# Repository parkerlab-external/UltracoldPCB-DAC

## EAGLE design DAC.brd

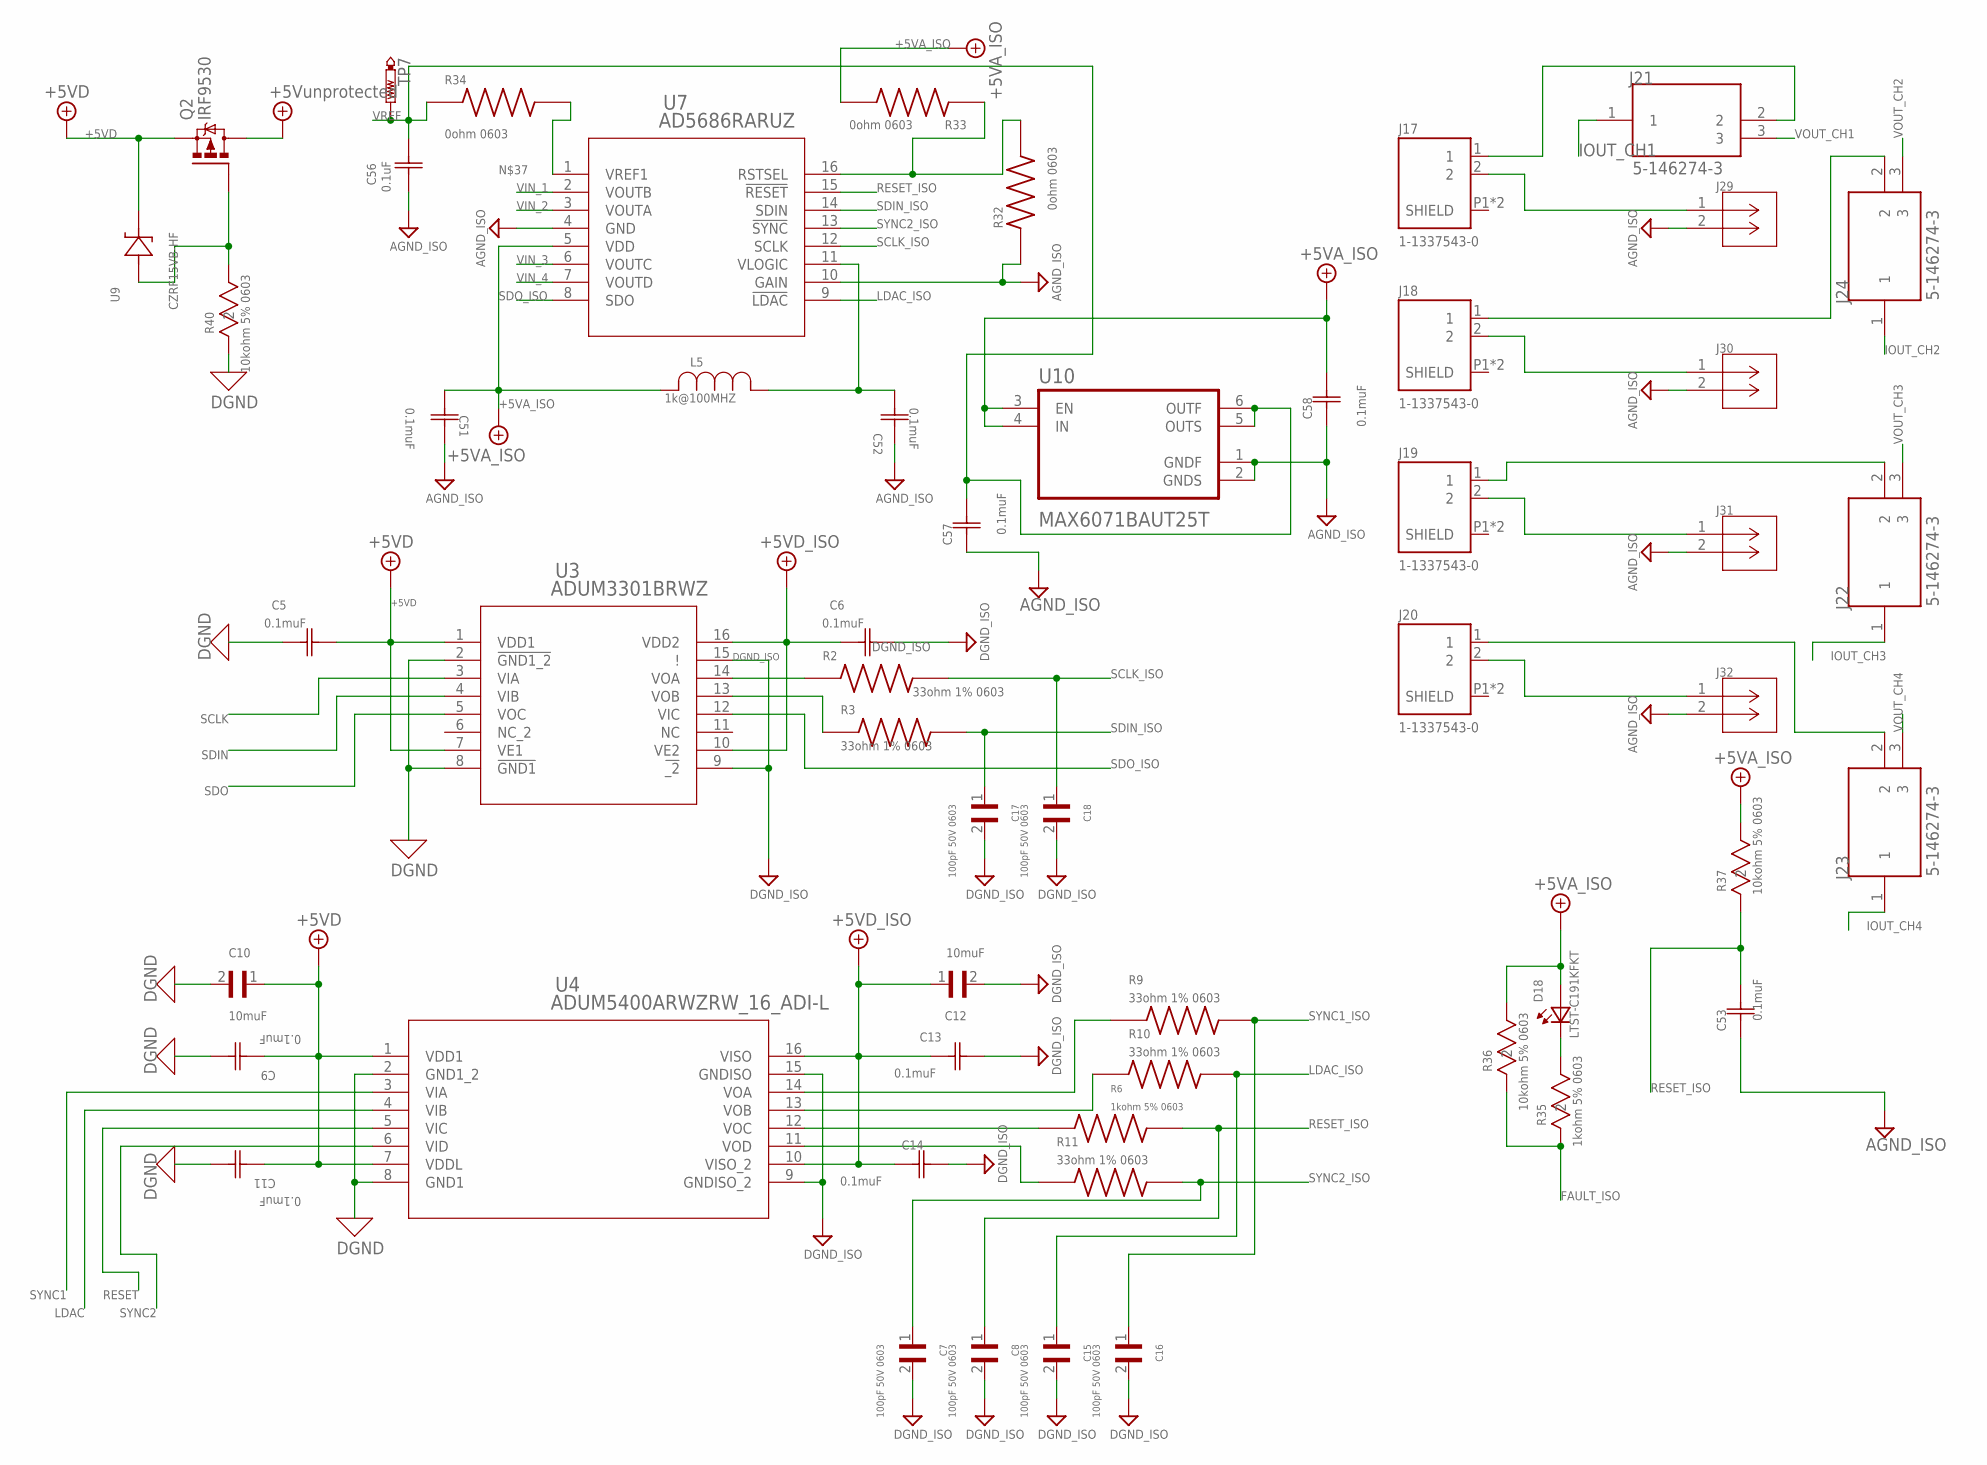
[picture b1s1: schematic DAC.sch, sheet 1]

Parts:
C5, C6, C9, C11, C13, C14, C51, C52, C53, C56, C57, C58: 0.1muF; G-188_MUR
C7, C8, C15, C16, C17, C18: 100pF 50V 0603; CAPC1608X90N
C10, C12: 10muF; CAPC2012X135N
D18: LTST-C191KFKT; 0603
J17, J18, J19, J20: 1-1337543-0; CONN_1-1337543-0
J21, J22, J23, J24: 5-146274-3; TE_5-146274-3
J29, J30, J31, J32: 61300211121; CONN_61300211121_WRE
L5: 1k@100MHZ; IND_BLM18_0603_MUR
Q2: IRF9530; TO220BV
R2, R3, R9, R10, R11: 33ohm 1% 0603; RESC1508X50N
R6: 1kohm 5% 0603; RESC1608X55N
R32, R33, R34: 0ohm 0603; RESC1608X55N
R35: 1kohm 5% 0603; RC0603N_PAN
R36, R37, R40: 10kohm 5% 0603; RC0603N_PAN
TP7: PTR1B1,27; B1,27
U3: ADUM3301BRWZ; RW_16_ADI
U4: ADUM5400ARWZRW_16_ADI-L; RW_16_ADI-L
U7: AD5686RARUZ; RU-16_ADI
U9: CZRF15VB-HF; CZRF
U10: MAX6071BAUT25T; SOT95P280X145-6N

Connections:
+5VA_ISO: C51.1, C58.2, D18.2 (A2), L5.2, R33.2, R36.1, R37.1, U7.5 (VDD), U10.3 (EN), U10.4 (IN); also elsewhere on the board
+5VD: C5.2, C9.1, C10.1, C11.1, Q2.S, U3.1 (VDD1), U3.7 (VE1), U4.1 (VDD1), U4.7 (VDDL), U9.1; also elsewhere on the board
+5VD_ISO: C6.1, C12.1, C13.1, C14.1, U3.10 (VE2), U3.16 (VDD2), U4.10 (VISO_2), U4.16 (VISO); also elsewhere on the board
+5V_UN: Q2.D
AGND_ISO: C51.2, C52.2, C53.1, C56.1, C57.1, C58.1, J29.2, J30.2, J31.2, J32.2, R32.1, U7.4 (GND), U7.10 (GAIN), U10.1 (GNDF), U10.2 (GNDS); also elsewhere on the board
DGND: C5.1, C9.2, C10.2, C11.2, R40.2, U3.2 (!GND1_2), U3.8 (!GND1), U4.2 (GND1_2), U4.8 (GND1); also elsewhere on the board
DGND_ISO: C6.2, C7.2, C8.2, C12.2, C13.2, C14.2, C15.2, C16.2, C17.2, C18.2, U3.9 (!_2), U3.15 (!), U4.9 (GNDISO_2), U4.15 (GNDISO); also elsewhere on the board
FAULT_ISO: R35.2, R36.2; also elsewhere on the board
IOUT_CH1: J21.1; also elsewhere on the board
IOUT_CH2: J24.1; also elsewhere on the board
IOUT_CH3: J22.1; also elsewhere on the board
IOUT_CH4: J23.1; also elsewhere on the board
LDAC: U4.4 (VIB); also elsewhere on the board
LDAC_ISO: C15.1, R10.2, U7.9 (!LDAC)
unnamed: C52.1, L5.1, U7.11 (VLOGIC)
unnamed: R9.1, U4.14 (VOA)
unnamed: R2.1, U3.14 (VOA)
unnamed: R3.1, U3.13 (VOB)
unnamed: R10.1, U4.13 (VOB)
unnamed: R6.1, U4.12 (VOC)
unnamed: R11.1, U4.11 (VOD)
unnamed: J17.2, J29.1
unnamed: D18.1 (K2), R35.1
unnamed: J18.2, J30.1
unnamed: R34.2, U7.1 (VREF1)
unnamed: J17.1, J21.2
unnamed: J18.1, J24.2
unnamed: J19.2, J31.1
unnamed: J19.1, J22.2
unnamed: J20.1, J23.2
unnamed: J20.2, J32.1
unnamed: Q2.G, R40.1, U9.2
unnamed: R32.2, R33.1, U7.16 (RSTSEL)
RESET: U4.5 (VIC); also elsewhere on the board
RESET_ISO: C8.1, C53.2, R6.2, R37.2, U7.15 (!RESET); also elsewhere on the board
SCLK: U3.3 (VIA); also elsewhere on the board
SCLK_ISO: C18.1, R2.2, U7.12 (SCLK); also elsewhere on the board
SDIN: U3.4 (VIB); also elsewhere on the board
SDIN_ISO: C17.1, R3.2, U7.14 (SDIN); also elsewhere on the board
SDO: U3.5 (VOC); also elsewhere on the board
SDO_ISO: U3.12 (VIC), U7.8 (SDO); also elsewhere on the board
SYNC1: U4.3 (VIA); also elsewhere on the board
SYNC1_ISO: C16.1, R9.2; also elsewhere on the board
SYNC2: U4.6 (VID); also elsewhere on the board
SYNC2_ISO: C7.1, R11.2, U7.13 (!SYNC)
VIN_1: U7.2 (VOUTB); also elsewhere on the board
VIN_2: U7.3 (VOUTA); also elsewhere on the board
VIN_3: U7.6 (VOUTC); also elsewhere on the board
VIN_4: U7.7 (VOUTD); also elsewhere on the board
VOUT_CH1: J21.3; also elsewhere on the board
VOUT_CH2: J24.3; also elsewhere on the board
VOUT_CH3: J22.3; also elsewhere on the board
VOUT_CH4: J23.3; also elsewhere on the board
VREF: C56.2, C57.2, R34.1, TP7.TP, U10.5 (OUTS), U10.6 (OUTF); also elsewhere on the board

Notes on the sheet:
0.1uF

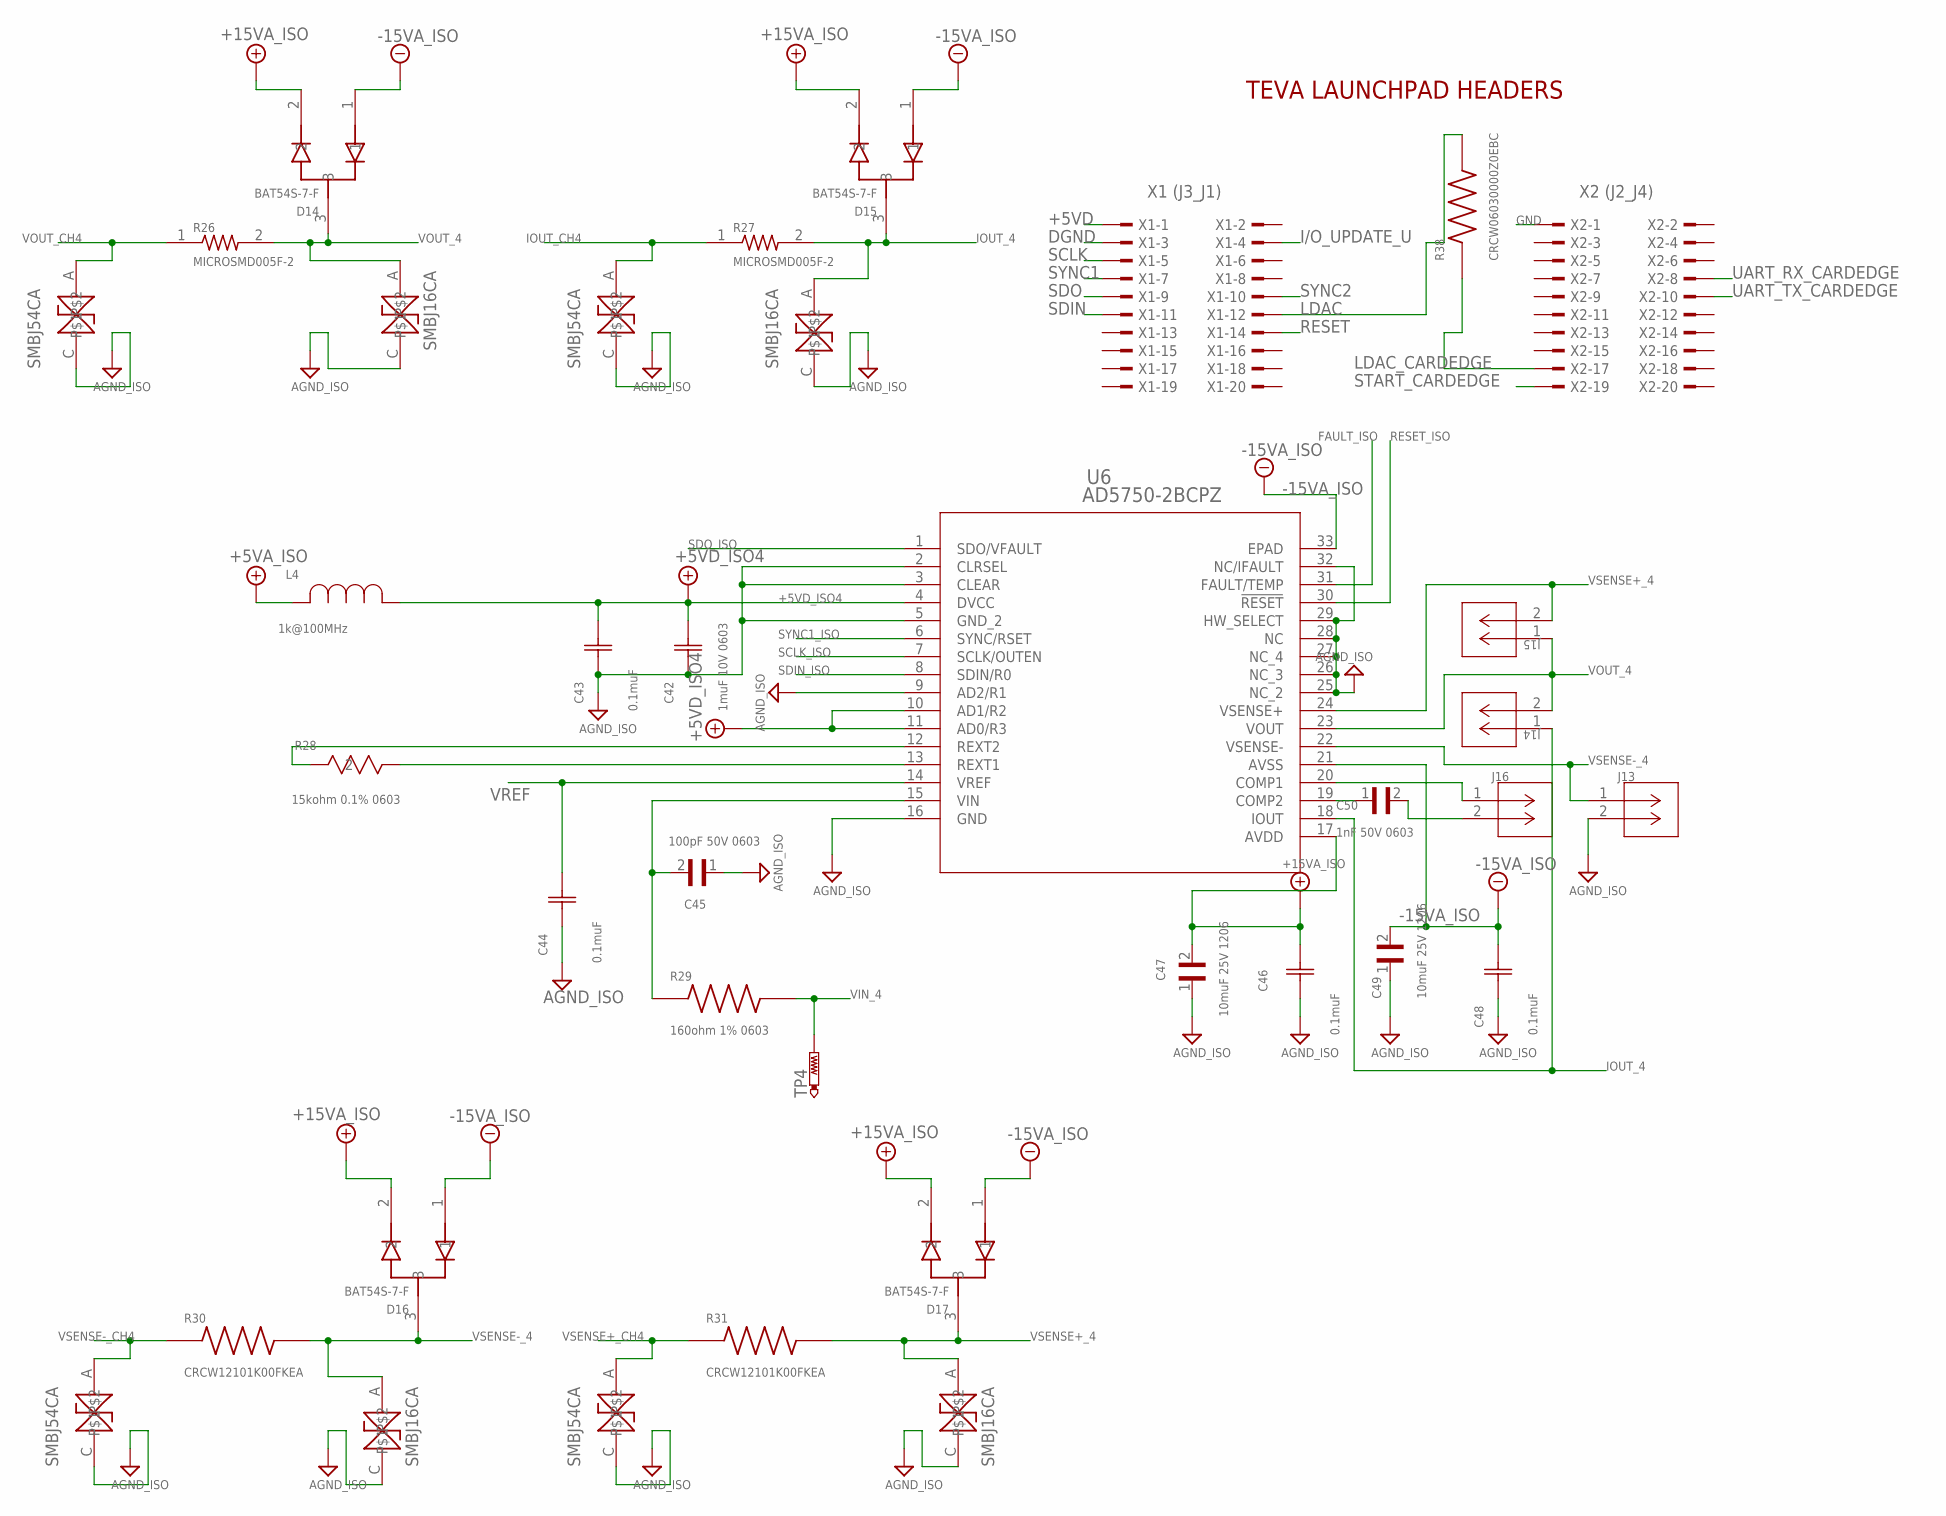
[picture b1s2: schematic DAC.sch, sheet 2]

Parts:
C42: 1muF 10V 0603; CAPC17595_90N_KEM
C43, C44, C46, C48: 0.1muF; G-188_MUR
C45: 100pF 50V 0603; CAPC1608X90N
C47, C49: 10muF 25V 1206; CAPC3216X180N
C50: 1nF 50V 0603; CAPC1608X90N
D14, D15, D16, D17: BAT54S-7-F; SOT95P240X110-3N
J13, J14, J15, J16: 61300211121; CONN_61300211121_WRE
L4: 1k@100MHz; IND_BLM18_0603_MUR
R26, R27: MICROSMD005F-2; RESC3125X65N
R28: 15kohm 0.1% 0603; RC0603N_PAN
R29: 160ohm 1% 0603; RESC1608X55N
R30, R31: CRCW12101K00FKEA; RESC3225X60N
R38: CRCW06030000Z0EBC; RESC1608X55N
TP4: PTR1B1,27; B1,27
TV1, TV2, TV4: 54_SMBJ54CA; DIOM5436X220N
TV3: SMBJ54CA; DIOM5436X220N
TV17, TV18, TV19, TV20: SMBJ16CA; DIOM5436X220N
U6: AD5750-2BCPZ; CP_32_7_ADI
X1: X1 (J3_J1); TSW-110-XX-G-D
X2: X2 (J2_J4); TSW-110-XX-G-D

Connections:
+5VA_ISO: L4.2; also elsewhere on the board
+5VD: X1.1; also elsewhere on the board
+5VD_ISO4: C42.2, C43.2, L4.1, U6.4 (DVCC), U6.10 (AD1/R2), U6.11 (AD0/R3)
+15VA_ISO: C46.2, C47.2, D14.2, D15.2, D16.2, D17.2, U6.17 (AVDD); also elsewhere on the board
-15VA_ISO: C48.2, C49.2, D14.1, D15.1, D16.1, D17.1, U6.21 (AVSS), U6.33 (EPAD); also elsewhere on the board
AGND_ISO: C42.1, C43.1, C44.1, C45.1, C46.1, C47.1, C48.1, C49.1, J13.2, TV1.C, TV2.C, TV3.C, TV4.C, TV17.C, TV18.C, TV19.C, TV20.C, U6.2 (CLRSEL), U6.3 (CLEAR), U6.5 (GND_2), U6.9 (AD2/R1), U6.16 (GND), U6.25 (NC_2), U6.26 (NC_3), U6.27 (NC_4), U6.28 (NC), U6.29 (HW_SELECT), U6.32 (NC/IFAULT); also elsewhere on the board
DGND: X1.3; also elsewhere on the board
FAULT_ISO: U6.31 (FAULT/TEMP); also elsewhere on the board
GND: X2.1
I/O_UPDATE_U: X1.4
IOUT_4: D15.3, J14.1, R27.2, TV18.A, U6.18 (IOUT)
IOUT_CH4: R27.1, TV2.A; also elsewhere on the board
LDAC: R38.2, X1.12; also elsewhere on the board
LDAC_CARDEDGE: R38.1, X2.17
unnamed: R28.2, U6.12 (REXT2)
unnamed: R28.1, U6.13 (REXT1)
unnamed: C45.2, R29.1, U6.15 (VIN)
unnamed: C50.1, U6.19 (COMP2)
unnamed: J16.1, U6.20 (COMP1)
unnamed: C50.2, J16.2
RESET: X1.14; also elsewhere on the board
RESET_ISO: U6.30 (!RESET); also elsewhere on the board
SCLK: X1.5; also elsewhere on the board
SCLK_ISO: U6.7 (SCLK/OUTEN); also elsewhere on the board
SDIN: X1.11; also elsewhere on the board
SDIN_ISO: U6.8 (SDIN/R0); also elsewhere on the board
SDO: X1.9; also elsewhere on the board
SDO_ISO: U6.1 (SDO/VFAULT); also elsewhere on the board
START_CARDEDGE: X2.19
SYNC1: X1.7; also elsewhere on the board
SYNC1_ISO: U6.6 (SYNC/RSET); also elsewhere on the board
SYNC2: X1.10; also elsewhere on the board
UART_RX_CARDEDGE: X2.8
UART_TX_CARDEDGE: X2.10
VIN_4: R29.2, TP4.TP; also elsewhere on the board
VOUT_4: D14.3, J14.2, J15.1, R26.2, TV17.A, U6.23 (VOUT)
VOUT_CH4: R26.1, TV1.A; also elsewhere on the board
VREF: C44.2, U6.14 (VREF); also elsewhere on the board
VSENSE+_4: D17.3, J15.2, R31.2, TV20.A, U6.24 (VSENSE+)
VSENSE+_CH4: R31.1, TV4.A
VSENSE-_4: D16.3, J13.1, R30.2, TV19.A, U6.22 (VSENSE-)
VSENSE-_CH4: R30.1, TV3.A

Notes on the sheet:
TEVA LAUNCHPAD HEADERS
SMBJ16CA
SMBJ54CA

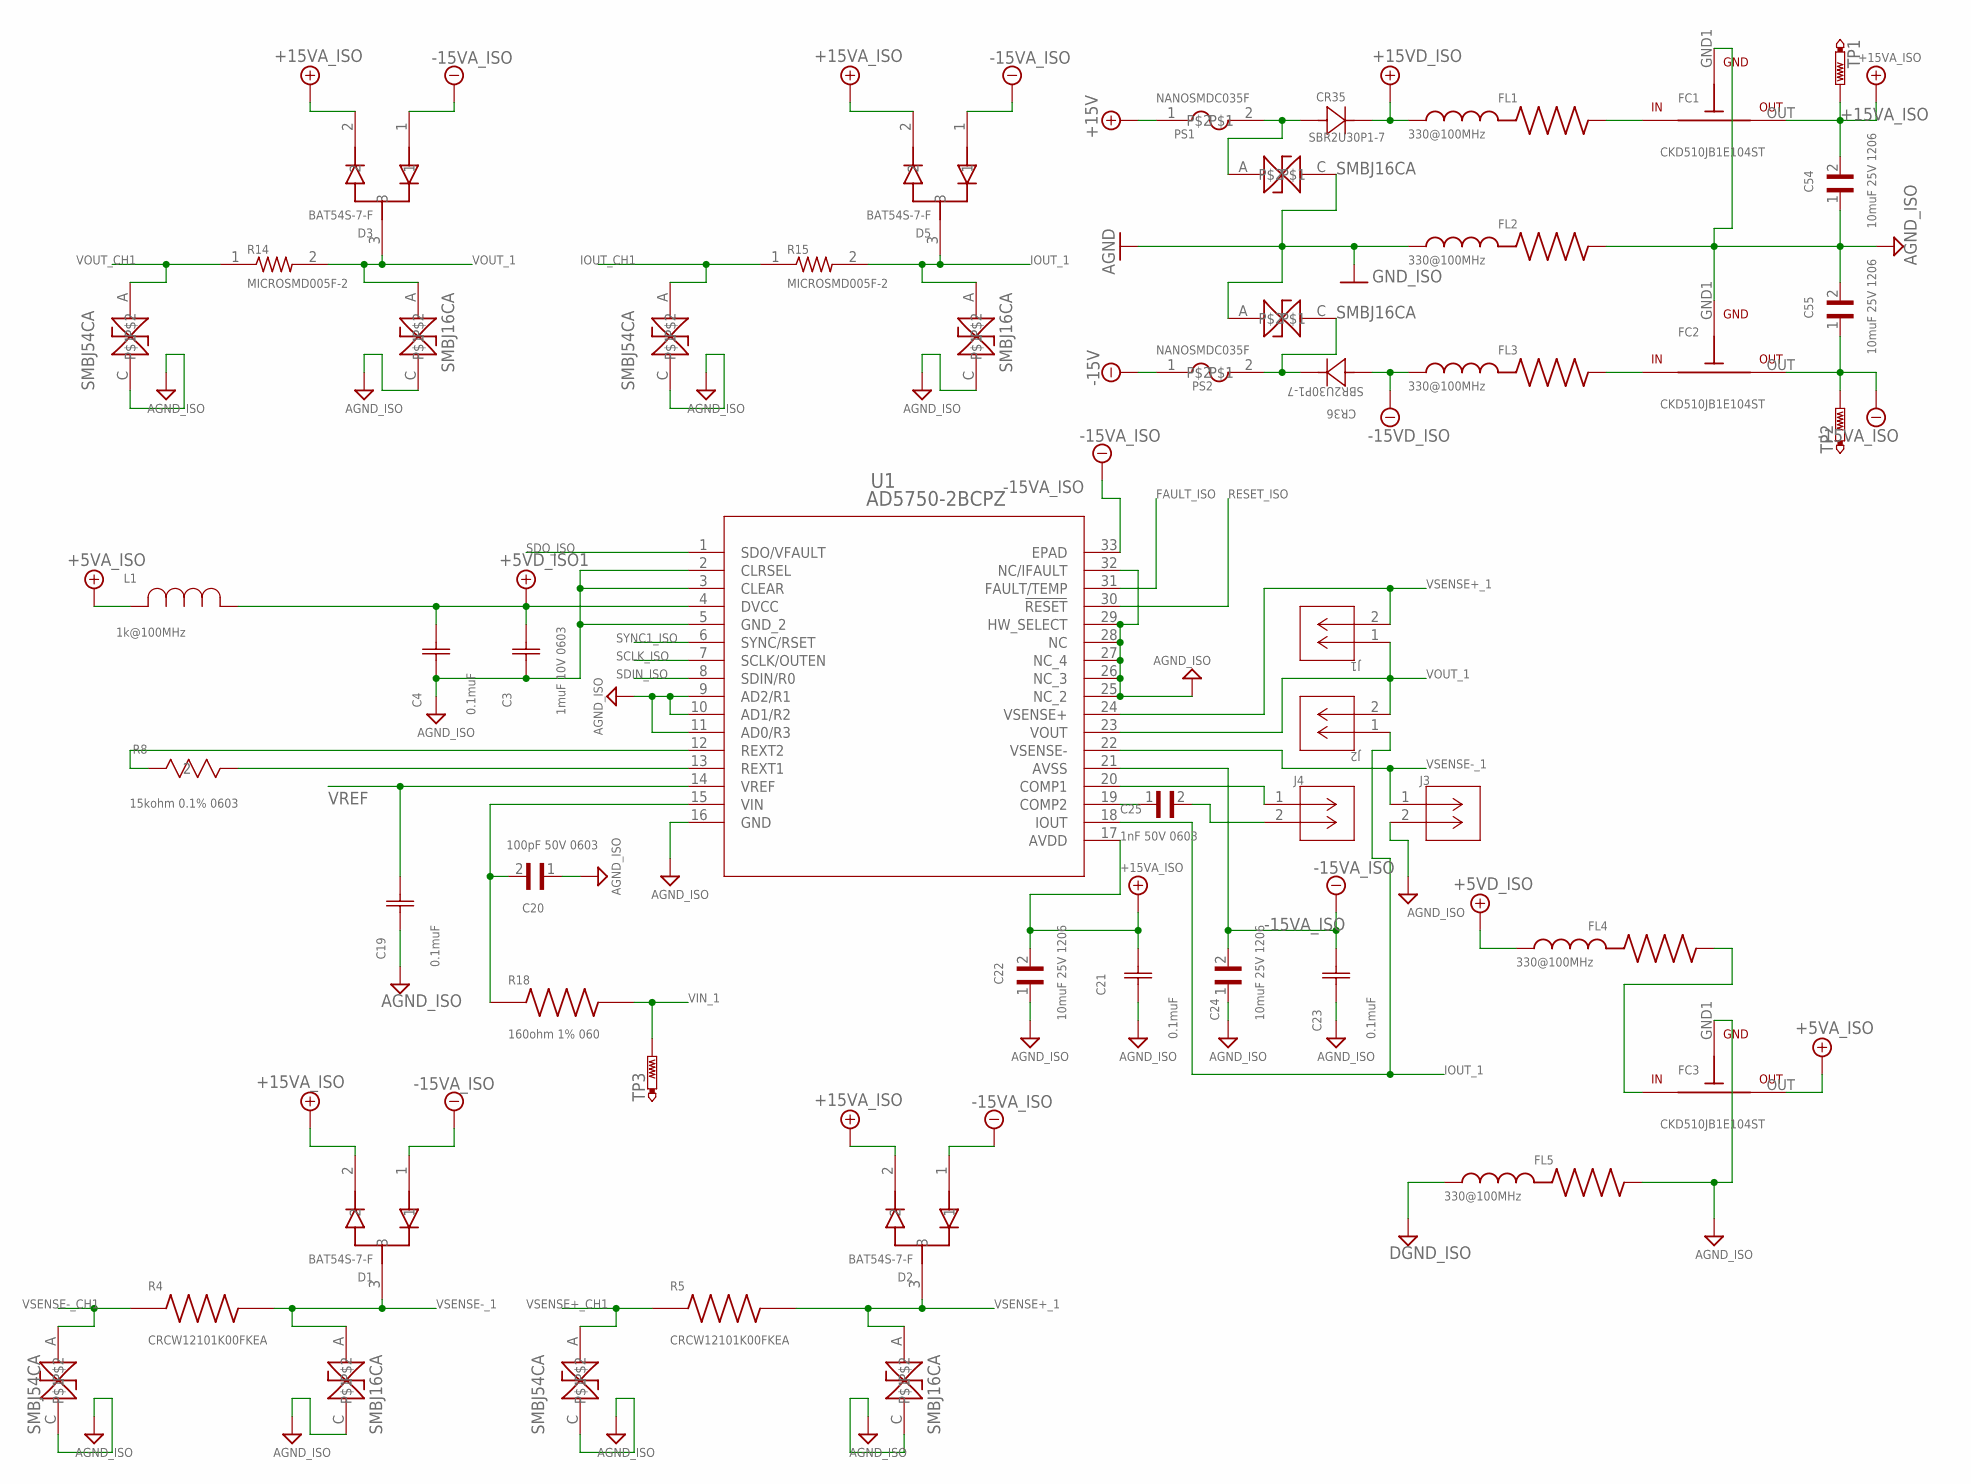
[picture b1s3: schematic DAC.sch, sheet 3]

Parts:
C3: 1muF 10V 0603; CAPC17595_90N_KEM
C4, C19, C21, C23: 0.1muF; G-188_MUR
C20: 100pF 50V 0603; CAPC1608X90N
C22, C24, C54, C55: 10muF 25V 1206; CAPC3216X180N
C25: 1nF 50V 0603; CAPC1608X90N
CR35, CR36: SBR2U30P1-7; DIODE_SBR3M30P1_1P78X2P8_DIO
D1, D2, D3, D5: BAT54S-7-F; SOT95P240X110-3N
FC1, FC2, FC3: F1-4; FCAP
FL1, FL2, FL3, FL4, FL5: 330@100MHz; BEADC2012X105N
J1, J2, J3, J4: 61300211121; CONN_61300211121_WRE
L1: 1k@100MHz; IND_BLM18_0603_MUR
PS1, PS2: POLYSWITCH; RESC3115X65N
R4, R5: CRCW12101K00FKEA; RESC3225X60N
R8: 15kohm 0.1% 0603; RC0603N_PAN
R14, R15: MICROSMD005F-2; RESC3125X65N
R18: 160ohm 1% 060; RESC1608X55N
TP1, TP2, TP3: PTR1B1,27; B1,27
TV5, TV6, TV7, TV8: 54_SMBJ54CA; DIOM5436X220N
TV21, TV22, TV23, TV24, TV33, TV34: SMBJ16CA; DIOM5436X220N
U1: AD5750-2BCPZ; CP_32_7_ADI

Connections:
+5VA_ISO: FC3.OUT, L1.2; also elsewhere on the board
+5VD_ISO: FL4.1; also elsewhere on the board
+5VD_ISO1: C3.2, C4.2, L1.1, U1.4 (DVCC)
+15V: PS1.1
+15VA_ISO: C21.2, C22.2, C54.2, D1.2, D2.2, D3.2, D5.2, FC1.OUT, TP1.TP, U1.17 (AVDD); also elsewhere on the board
+15VD_ISO: CR35.1, FL1.1
-15V: PS2.1
-15VA_ISO: C23.2, C24.2, C55.1, D1.1, D2.1, D3.1, D5.1, FC2.OUT, TP2.TP, U1.21 (AVSS), U1.33 (EPAD); also elsewhere on the board
-15VD_ISO: CR36.2, FL3.1
AGND: FL2.1, TV33.C, TV34.A
AGND_ISO: C3.1, C4.1, C19.1, C20.1, C21.1, C22.1, C23.1, C24.1, C54.1, C55.2, FC1.GND1, FC2.GND1, FC3.GND1, FL2.2, FL5.2, J3.2, TV5.C, TV6.C, TV7.C, TV8.C, TV21.C, TV22.C, TV23.C, TV24.C, U1.2 (CLRSEL), U1.3 (CLEAR), U1.5 (GND_2), U1.9 (AD2/R1), U1.10 (AD1/R2), U1.11 (AD0/R3), U1.16 (GND), U1.25 (NC_2), U1.26 (NC_3), U1.27 (NC_4), U1.28 (NC), U1.29 (HW_SELECT), U1.32 (NC/IFAULT); also elsewhere on the board
DGND_ISO: FL5.1; also elsewhere on the board
FAULT_ISO: U1.31 (FAULT/TEMP); also elsewhere on the board
IOUT_1: D5.3, J2.1, R15.2, TV22.A, U1.18 (IOUT)
IOUT_CH1: R15.1, TV6.A; also elsewhere on the board
unnamed: C20.2, R18.1, U1.15 (VIN)
unnamed: C25.1, U1.19 (COMP2)
unnamed: J4.1, U1.20 (COMP1)
unnamed: C25.2, J4.2
unnamed: R8.2, U1.12 (REXT2)
unnamed: R8.1, U1.13 (REXT1)
unnamed: FC3.IN, FL4.2
unnamed: CR35.2, PS1.2, TV33.A
unnamed: FC1.IN, FL1.2
unnamed: CR36.1, PS2.2, TV34.C
unnamed: FC2.IN, FL3.2
RESET_ISO: U1.30 (!RESET); also elsewhere on the board
SCLK_ISO: U1.7 (SCLK/OUTEN); also elsewhere on the board
SDIN_ISO: U1.8 (SDIN/R0); also elsewhere on the board
SDO_ISO: U1.1 (SDO/VFAULT); also elsewhere on the board
SYNC1_ISO: U1.6 (SYNC/RSET); also elsewhere on the board
VIN_1: R18.2, TP3.TP; also elsewhere on the board
VOUT_1: D3.3, J1.1, J2.2, R14.2, TV21.A, U1.23 (VOUT)
VOUT_CH1: R14.1, TV5.A; also elsewhere on the board
VREF: C19.2, U1.14 (VREF); also elsewhere on the board
VSENSE+_1: D2.3, J1.2, R5.2, TV24.A, U1.24 (VSENSE+)
VSENSE+_CH1: R5.1, TV8.A
VSENSE-_1: D1.3, J3.1, R4.2, TV23.A, U1.22 (VSENSE-)
VSENSE-_CH1: R4.1, TV7.A

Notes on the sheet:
SMBJ16CA
SMBJ54CA
NANOSMDC035F
CKD510JB1E104ST
PS1
PS2
FC1
FC2
FC3

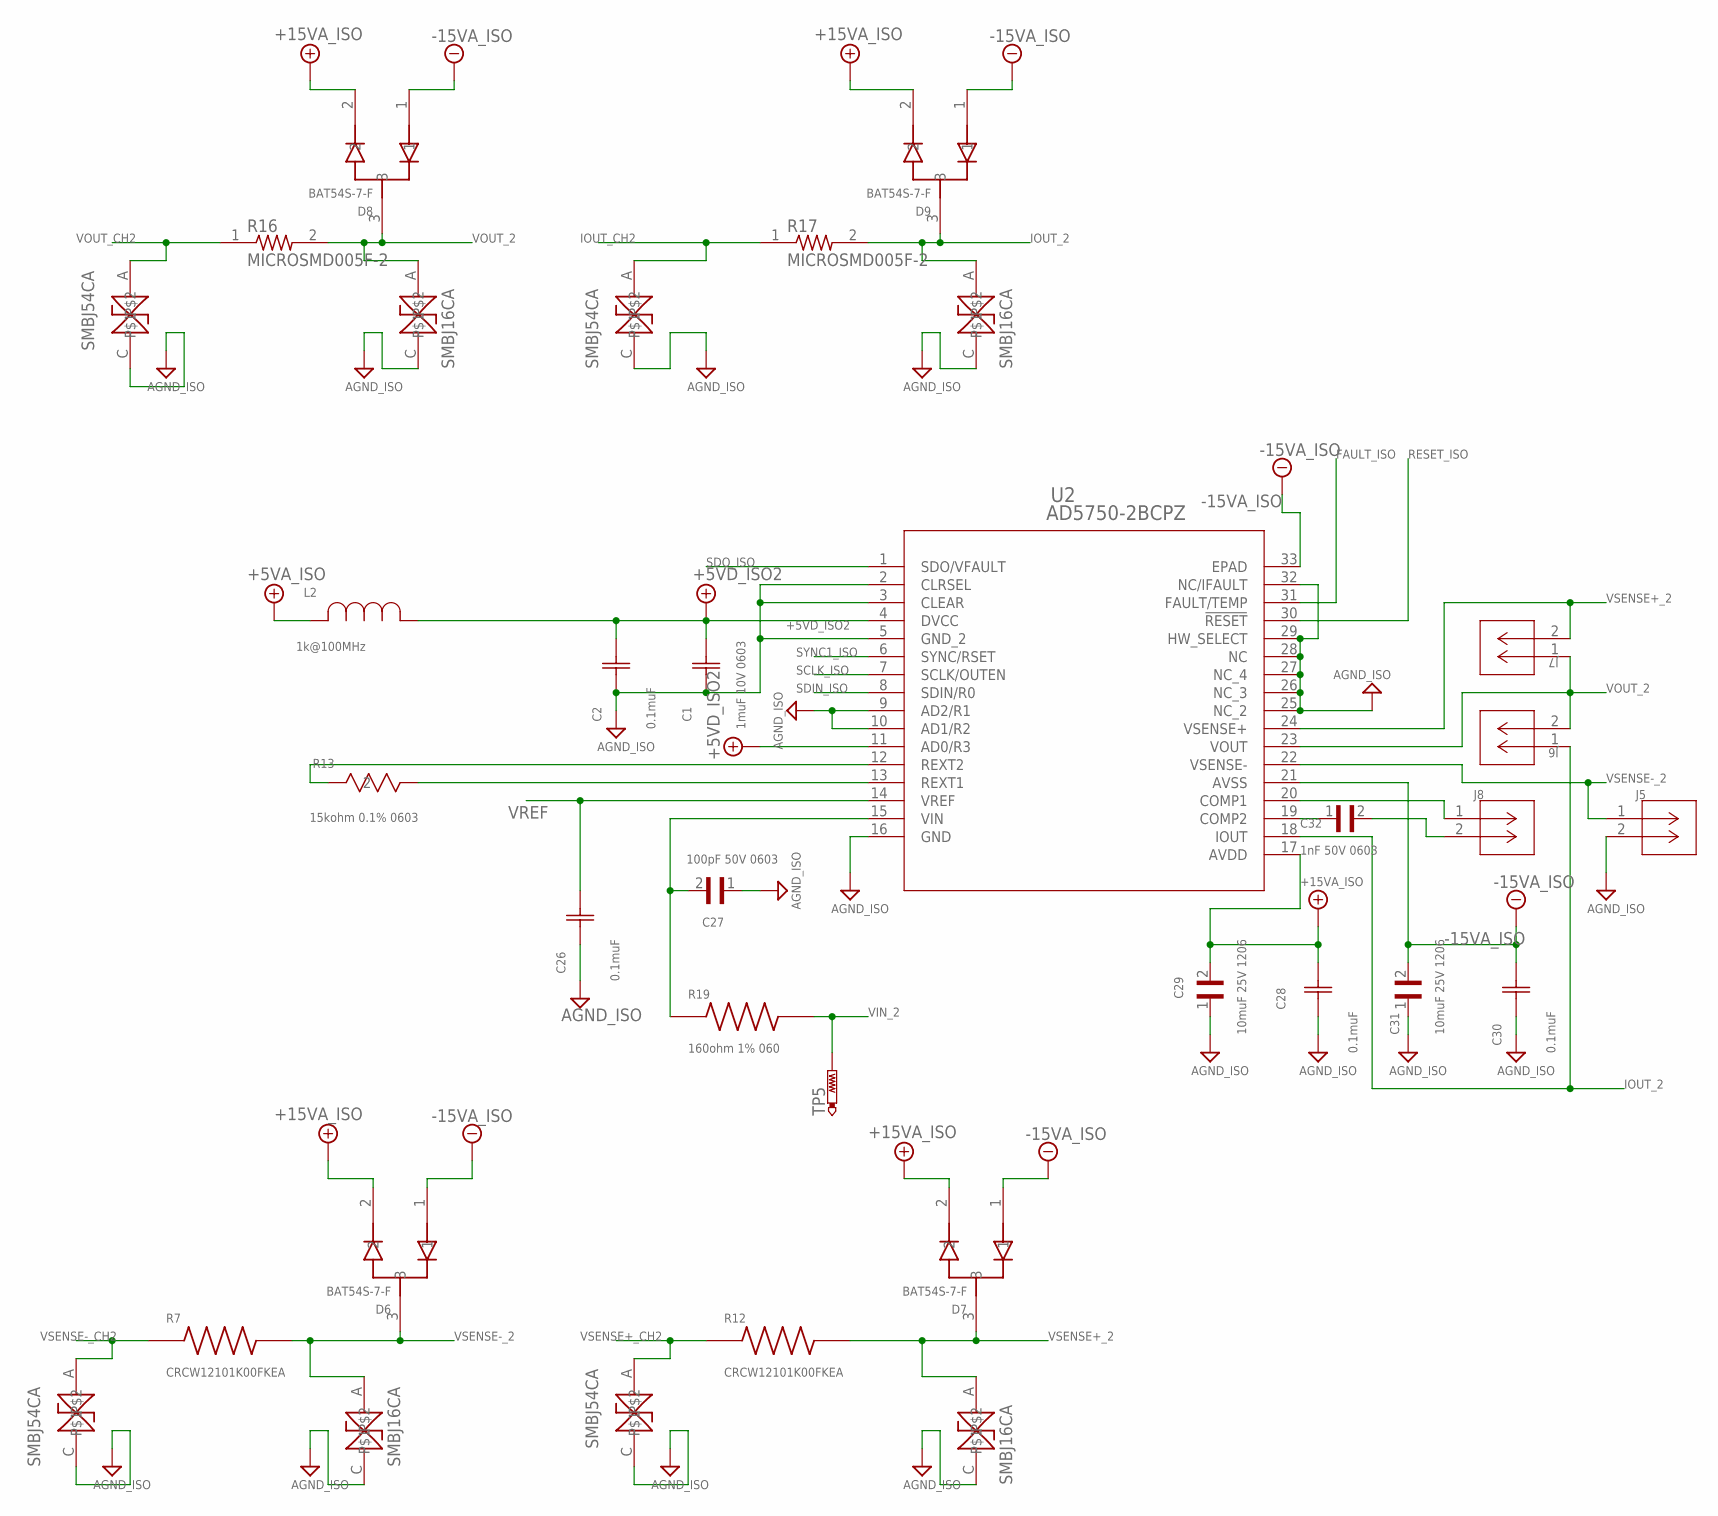
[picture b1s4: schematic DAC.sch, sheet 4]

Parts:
C1: 1muF 10V 0603; CAPC17595_90N_KEM
C2, C26, C28, C30: 0.1muF; G-188_MUR
C27: 100pF 50V 0603; CAPC1608X90N
C29, C31: 10muF 25V 1206; CAPC3216X180N
C32: 1nF 50V 0603; CAPC1608X90N
D6, D7, D8, D9: BAT54S-7-F; SOT95P240X110-3N
J5, J6, J7, J8: 61300211121; CONN_61300211121_WRE
L2: 1k@100MHz; IND_BLM18_0603_MUR
R7, R12: CRCW12101K00FKEA; RESC3225X60N
R13: 15kohm 0.1% 0603; RC0603N_PAN
R16, R17: MICROSMD005F-2; RESC3125X65N
R19: 160ohm 1% 060; RESC1608X55N
TP5: PTR1B1,27; B1,27
TV9, TV10, TV11, TV12: 54_SMBJ54CA; DIOM5436X220N
TV25, TV26, TV27, TV28: SMBJ16CA; DIOM5436X220N
U2: AD5750-2BCPZ; CP_32_7_ADI

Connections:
+5VA_ISO: L2.2; also elsewhere on the board
+5VD_ISO2: C1.2, C2.2, L2.1, U2.4 (DVCC), U2.11 (AD0/R3)
+15VA_ISO: C28.2, C29.2, D6.2, D7.2, D8.2, D9.2, U2.17 (AVDD); also elsewhere on the board
-15VA_ISO: C30.2, C31.2, D6.1, D7.1, D8.1, D9.1, U2.21 (AVSS), U2.33 (EPAD); also elsewhere on the board
AGND_ISO: C1.1, C2.1, C26.1, C27.1, C28.1, C29.1, C30.1, C31.1, J5.2, TV9.C, TV10.C, TV11.C, TV12.C, TV25.C, TV26.C, TV27.C, TV28.C, U2.2 (CLRSEL), U2.3 (CLEAR), U2.5 (GND_2), U2.9 (AD2/R1), U2.10 (AD1/R2), U2.16 (GND), U2.25 (NC_2), U2.26 (NC_3), U2.27 (NC_4), U2.28 (NC), U2.29 (HW_SELECT), U2.32 (NC/IFAULT); also elsewhere on the board
FAULT_ISO: U2.31 (FAULT/TEMP); also elsewhere on the board
IOUT_2: D9.3, J6.1, R17.2, TV26.A, U2.18 (IOUT)
IOUT_CH2: R17.1, TV10.A; also elsewhere on the board
unnamed: R13.2, U2.12 (REXT2)
unnamed: R13.1, U2.13 (REXT1)
unnamed: C27.2, R19.1, U2.15 (VIN)
unnamed: C32.1, U2.19 (COMP2)
unnamed: J8.1, U2.20 (COMP1)
unnamed: C32.2, J8.2
RESET_ISO: U2.30 (!RESET); also elsewhere on the board
SCLK_ISO: U2.7 (SCLK/OUTEN); also elsewhere on the board
SDIN_ISO: U2.8 (SDIN/R0); also elsewhere on the board
SDO_ISO: U2.1 (SDO/VFAULT); also elsewhere on the board
SYNC1_ISO: U2.6 (SYNC/RSET); also elsewhere on the board
VIN_2: R19.2, TP5.TP; also elsewhere on the board
VOUT_2: D8.3, J6.2, J7.1, R16.2, TV25.A, U2.23 (VOUT)
VOUT_CH2: R16.1, TV9.A; also elsewhere on the board
VREF: C26.2, U2.14 (VREF); also elsewhere on the board
VSENSE+_2: D7.3, J7.2, R12.2, TV28.A, U2.24 (VSENSE+)
VSENSE+_CH2: R12.1, TV12.A
VSENSE-_2: D6.3, J5.1, R7.2, TV27.A, U2.22 (VSENSE-)
VSENSE-_CH2: R7.1, TV11.A

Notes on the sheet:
SMBJ16CA
SMBJ54CA

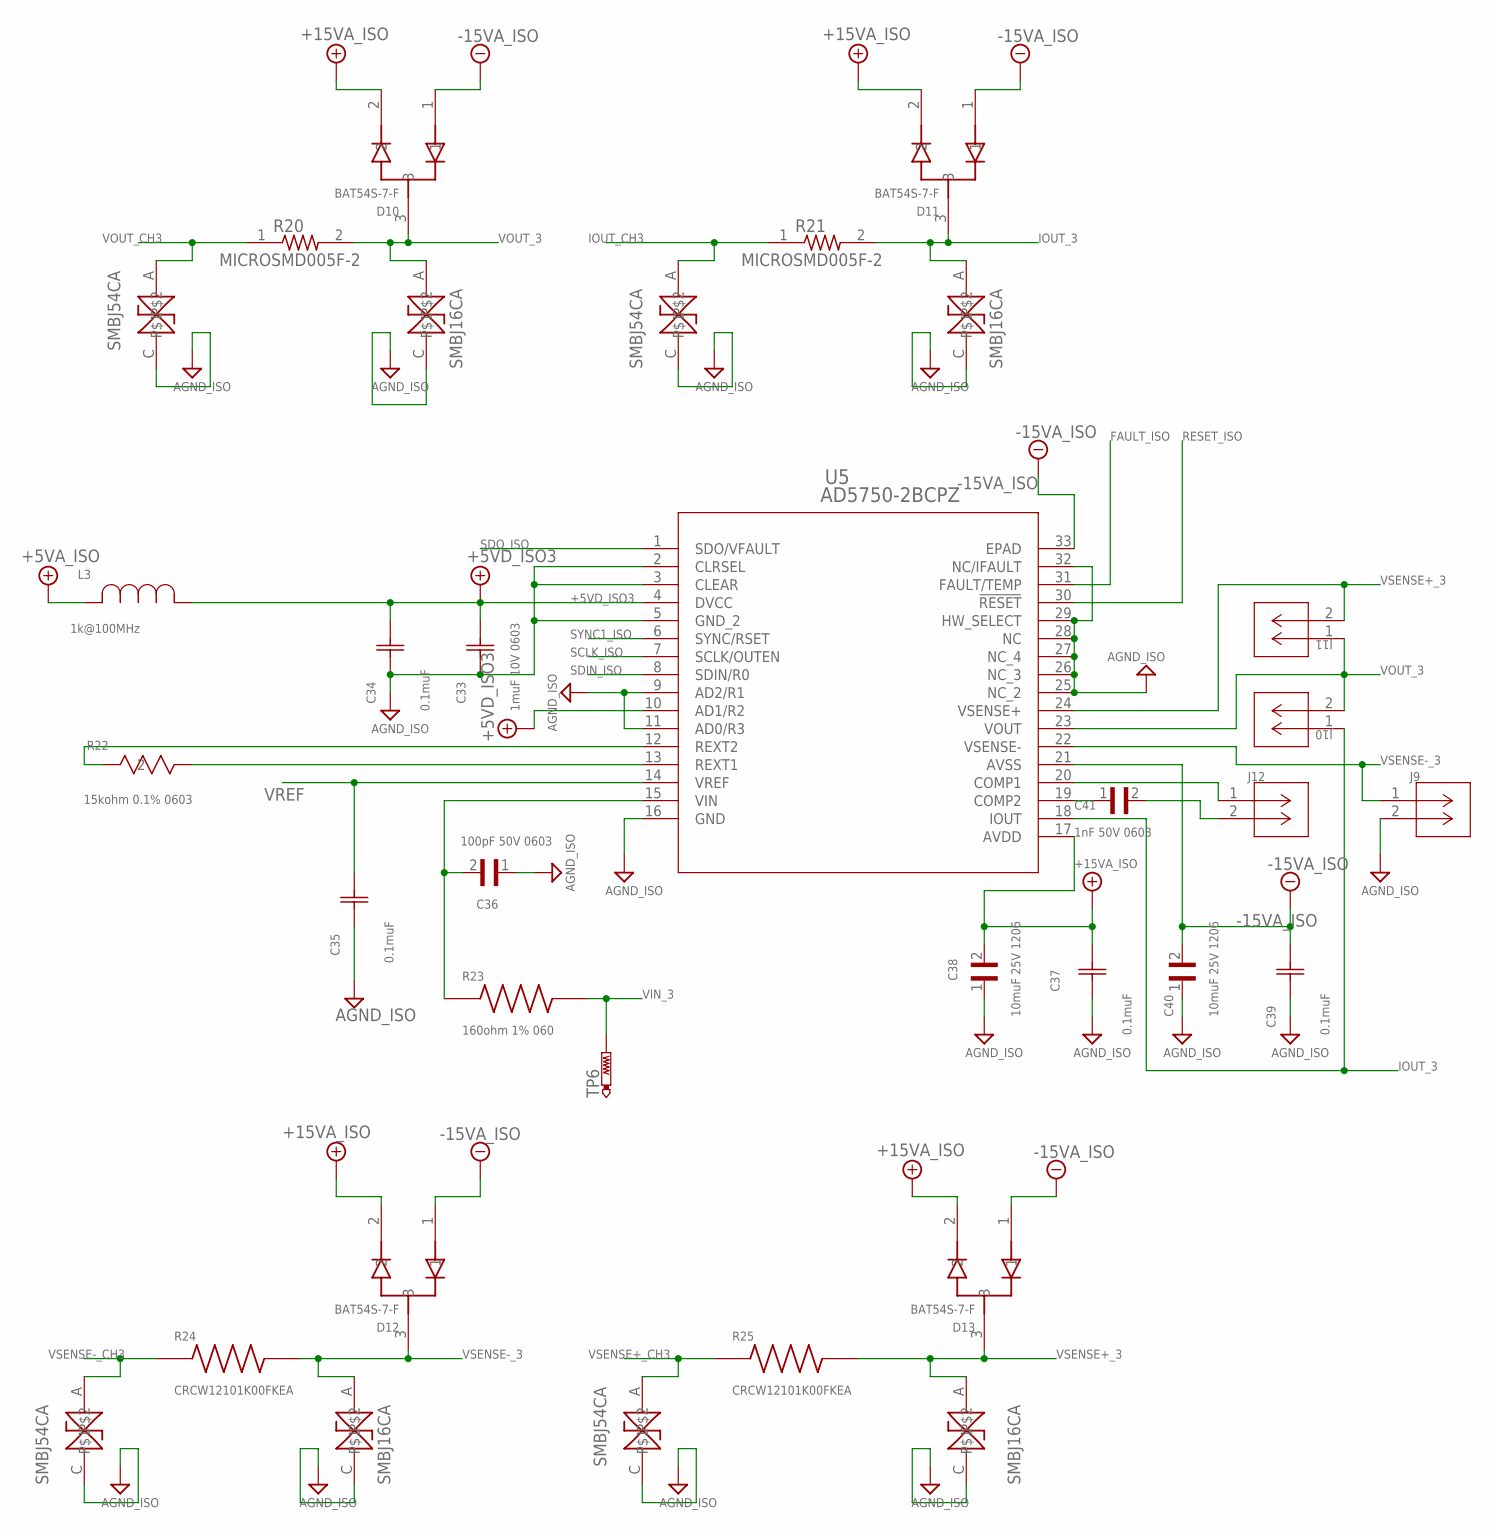
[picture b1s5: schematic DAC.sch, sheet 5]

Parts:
C33: 1muF 10V 0603; CAPC17595_90N_KEM
C34, C35, C37, C39: 0.1muF; G-188_MUR
C36: 100pF 50V 0603; CAPC1608X90N
C38, C40: 10muF 25V 1206; CAPC3216X180N
C41: 1nF 50V 0603; CAPC1608X90N
D10, D11, D12, D13: BAT54S-7-F; SOT95P240X110-3N
J9, J10, J11, J12: 61300211121; CONN_61300211121_WRE
L3: 1k@100MHz; IND_BLM18_0603_MUR
R20, R21: MICROSMD005F-2; RESC3125X65N
R22: 15kohm 0.1% 0603; RC0603N_PAN
R23: 160ohm 1% 060; RESC1608X55N
R24, R25: CRCW12101K00FKEA; RESC3225X60N
TP6: PTR1B1,27; B1,27
TV13, TV14, TV15, TV16: 54_SMBJ54CA; DIOM5436X220N
TV29, TV30, TV31, TV32: SMBJ16CA; DIOM5436X220N
U5: AD5750-2BCPZ; CP_32_7_ADI

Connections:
+5VA_ISO: L3.2; also elsewhere on the board
+5VD_ISO3: C33.2, C34.2, L3.1, U5.4 (DVCC), U5.10 (AD1/R2)
+15VA_ISO: C37.2, C38.2, D10.2, D11.2, D12.2, D13.2, U5.17 (AVDD); also elsewhere on the board
-15VA_ISO: C39.2, C40.2, D10.1, D11.1, D12.1, D13.1, U5.21 (AVSS), U5.33 (EPAD); also elsewhere on the board
AGND_ISO: C33.1, C34.1, C35.1, C36.1, C37.1, C38.1, C39.1, C40.1, J9.2, TV13.C, TV14.C, TV15.C, TV16.C, TV29.C, TV30.C, TV31.C, TV32.C, U5.2 (CLRSEL), U5.3 (CLEAR), U5.5 (GND_2), U5.9 (AD2/R1), U5.11 (AD0/R3), U5.16 (GND), U5.25 (NC_2), U5.26 (NC_3), U5.27 (NC_4), U5.28 (NC), U5.29 (HW_SELECT), U5.32 (NC/IFAULT); also elsewhere on the board
FAULT_ISO: U5.31 (FAULT/TEMP); also elsewhere on the board
IOUT_3: D11.3, J10.1, R21.2, TV30.A, U5.18 (IOUT)
IOUT_CH3: R21.1, TV14.A; also elsewhere on the board
unnamed: R22.2, U5.12 (REXT2)
unnamed: R22.1, U5.13 (REXT1)
unnamed: C36.2, R23.1, U5.15 (VIN)
unnamed: C41.1, U5.19 (COMP2)
unnamed: J12.1, U5.20 (COMP1)
unnamed: C41.2, J12.2
RESET_ISO: U5.30 (!RESET); also elsewhere on the board
SCLK_ISO: U5.7 (SCLK/OUTEN); also elsewhere on the board
SDIN_ISO: U5.8 (SDIN/R0); also elsewhere on the board
SDO_ISO: U5.1 (SDO/VFAULT); also elsewhere on the board
SYNC1_ISO: U5.6 (SYNC/RSET); also elsewhere on the board
VIN_3: R23.2, TP6.TP; also elsewhere on the board
VOUT_3: D10.3, J10.2, J11.1, R20.2, TV29.A, U5.23 (VOUT)
VOUT_CH3: R20.1, TV13.A; also elsewhere on the board
VREF: C35.2, U5.14 (VREF); also elsewhere on the board
VSENSE+_3: D13.3, J11.2, R25.2, TV32.A, U5.24 (VSENSE+)
VSENSE+_CH3: R25.1, TV16.A
VSENSE-_3: D12.3, J9.1, R24.2, TV31.A, U5.22 (VSENSE-)
VSENSE-_CH3: R24.1, TV15.A

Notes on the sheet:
SMBJ16CA
SMBJ54CA

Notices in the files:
parts and their libraries:
COPYRIGHT: Copyright (C) 2018 Accelerated Designs. All rights reserved
COPYRIGHT: Copyright (C) 2016 Accelerated Designs. All rights reserved
COPYRIGHT: Copyright (C) 2015 Accelerated Designs. All rights reserved
